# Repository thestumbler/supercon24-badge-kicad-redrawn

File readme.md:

# Redrawing Hackaday Supercon 2024 Badge in Kicad

Making a KiCad version of the Supercon 2024 Badge.
See the background story in this [Hackaday article](
https://hackaday.com/2024/10/31/supercon-2024-flower-sao-badge-redrawing-in-kicad).

* [Schematic drawing (PDF)](badge24-schematic.pdf))
* [PCB top drawing (PDF)](badge24-pcb-top.pdf)
* [PCB bottom drawing (PDF)](badge24-pcb-bot.pdf)

## Original Drawings

* [Schematic drawing (PDF)](badge24-original-sch.pdf)
* [PCB top drawing (PDF)](badge24-original-pcb-top.pdf)
* [PCB bottom drawing (PDF)](badge24-original-pcb-bot.pdf)

* [Assembly BOM (XLSX)](badge24-original-and-petal-matrix-bom.xlsx)

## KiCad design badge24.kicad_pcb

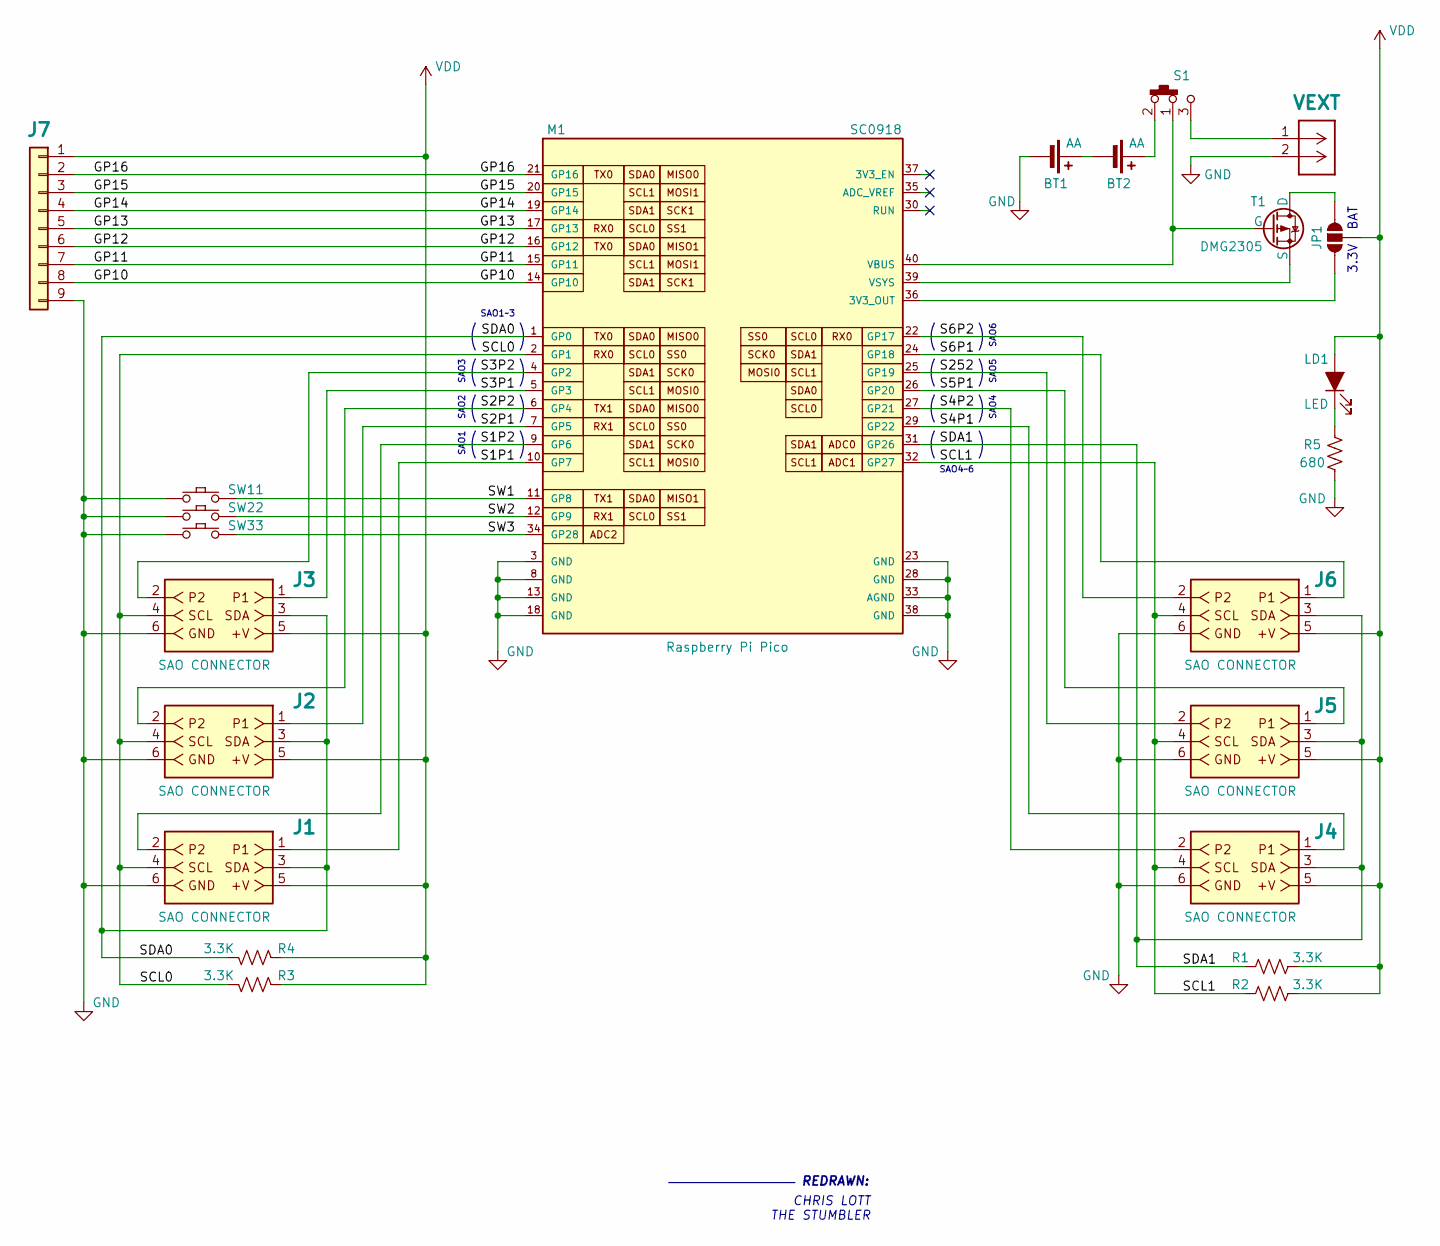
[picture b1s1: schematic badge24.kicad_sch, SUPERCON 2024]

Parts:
BT1, BT2: AA; BatteryHolder_Keystone_2460_1xAA_SAO
J1, J2, J3, J4, J5, J6: SAO CONNECTOR; SAO_PIN_HEADER_2x03
J7: Conn_01x09; IO_SAO_1x09_SMD_EXTERNAL
J99: VEXT; SAO_PinHeader_1x02_P2.54mm_SMD
JP1: SolderJumper_3_Open; SolderJumper_Open_Rounded_SAO
LD1: LED; LED_0805_2012Metric
M1: SC0918; RPi_Pico_SMD_SAO; PARTREV 1.6
R1, R2, R3, R4: 3.3K; R_0603_1608Metric_SAO
R5: 680; R_0603_1608Metric_SAO
S1: SW_Slide_SPDT; SW_Slide-03_Wuerth-WS-SLTV_10x2.5x6.4_P2.54mm
SW11, SW22, SW33: SW_Push; SW_SPST_PTS645_SAO
T1: DMG2305; SOT-23_SAO

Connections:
/GP10: J7.8, M1.14 (GP10)
/GP11: J7.7, M1.15 (GP11)
/GP12: J7.6, M1.16 (GP12)
/GP13: J7.5, M1.17 (GP13)
/GP14: J7.4, M1.19 (GP14)
/GP15: J7.3, M1.20 (GP15)
/GP16: J7.2, M1.21 (GP16)
/S1P1: J1.1, M1.10 (GP7)
/S1P2: J1.2, M1.9 (GP6)
/S2P1: J2.1, M1.7 (GP5)
/S2P2: J2.2, M1.6 (GP4)
/S3P1: J3.1, M1.5 (GP3)
/S3P2: J3.2, M1.4 (GP2)
/S4P1: J4.1, M1.29 (GP22)
/S4P2: J4.2, M1.27 (GP21)
/S5P1: J5.1, M1.26 (GP20)
/S6P1: J6.1, M1.24 (GP18)
/S6P2: J6.2, M1.22 (GP17)
/S252: J5.2, M1.25 (GP19)
/SCL0: J1.4, J2.4, J3.4, M1.2 (GP1), R3.2
/SCL1: J4.4, J5.4, J6.4, M1.32 (GP27), R2.1
/SDA0: J1.3, J2.3, J3.3, M1.1 (GP0), R4.2
/SDA1: J4.3, J5.3, J6.3, M1.31 (GP26), R1.1
/SW1: M1.11 (GP8), SW11.2
/SW2: M1.12 (GP9), SW22.2
/SW3: M1.34 (GP28), SW33.1
GND: BT1.2 (-), J1.6, J2.6, J3.6, J4.6, J5.6, J6.6, J7.9, J99.2, M1.3 (GND), M1.8 (GND), M1.13 (GND), M1.18 (GND), M1.23 (GND), M1.28 (GND), M1.33 (AGND), M1.38 (GND), R5.2, SW11.1, SW22.1, SW33.2
unnamed: BT1.1 (+), BT2.2 (-)
unnamed: BT2.1 (+), S1.2 (A)
unnamed: J99.1, S1.3 (B)
unnamed: JP1.1 (A), T1.3 (D)
unnamed: JP1.3 (B), M1.36 (3V3_OUT)
unnamed: LD1.1 (K), R5.1
unnamed: M1.40 (VBUS), S1.1 (C), T1.1 (G)
unnamed: M1.39 (VSYS), T1.2 (S)
VDD: J1.5, J2.5, J3.5, J4.5, J5.5, J6.5, J7.1, JP1.2 (C), LD1.2 (A), R1.2, R2.2, R3.1, R4.1

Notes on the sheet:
SAO4
REDRAWN:
SAO5
SAO1
BAT
SAO6
SAO3
SAO4~6
3.3V
CHRIS LOTT THE STUMBLER
SAO2
SAO1~3

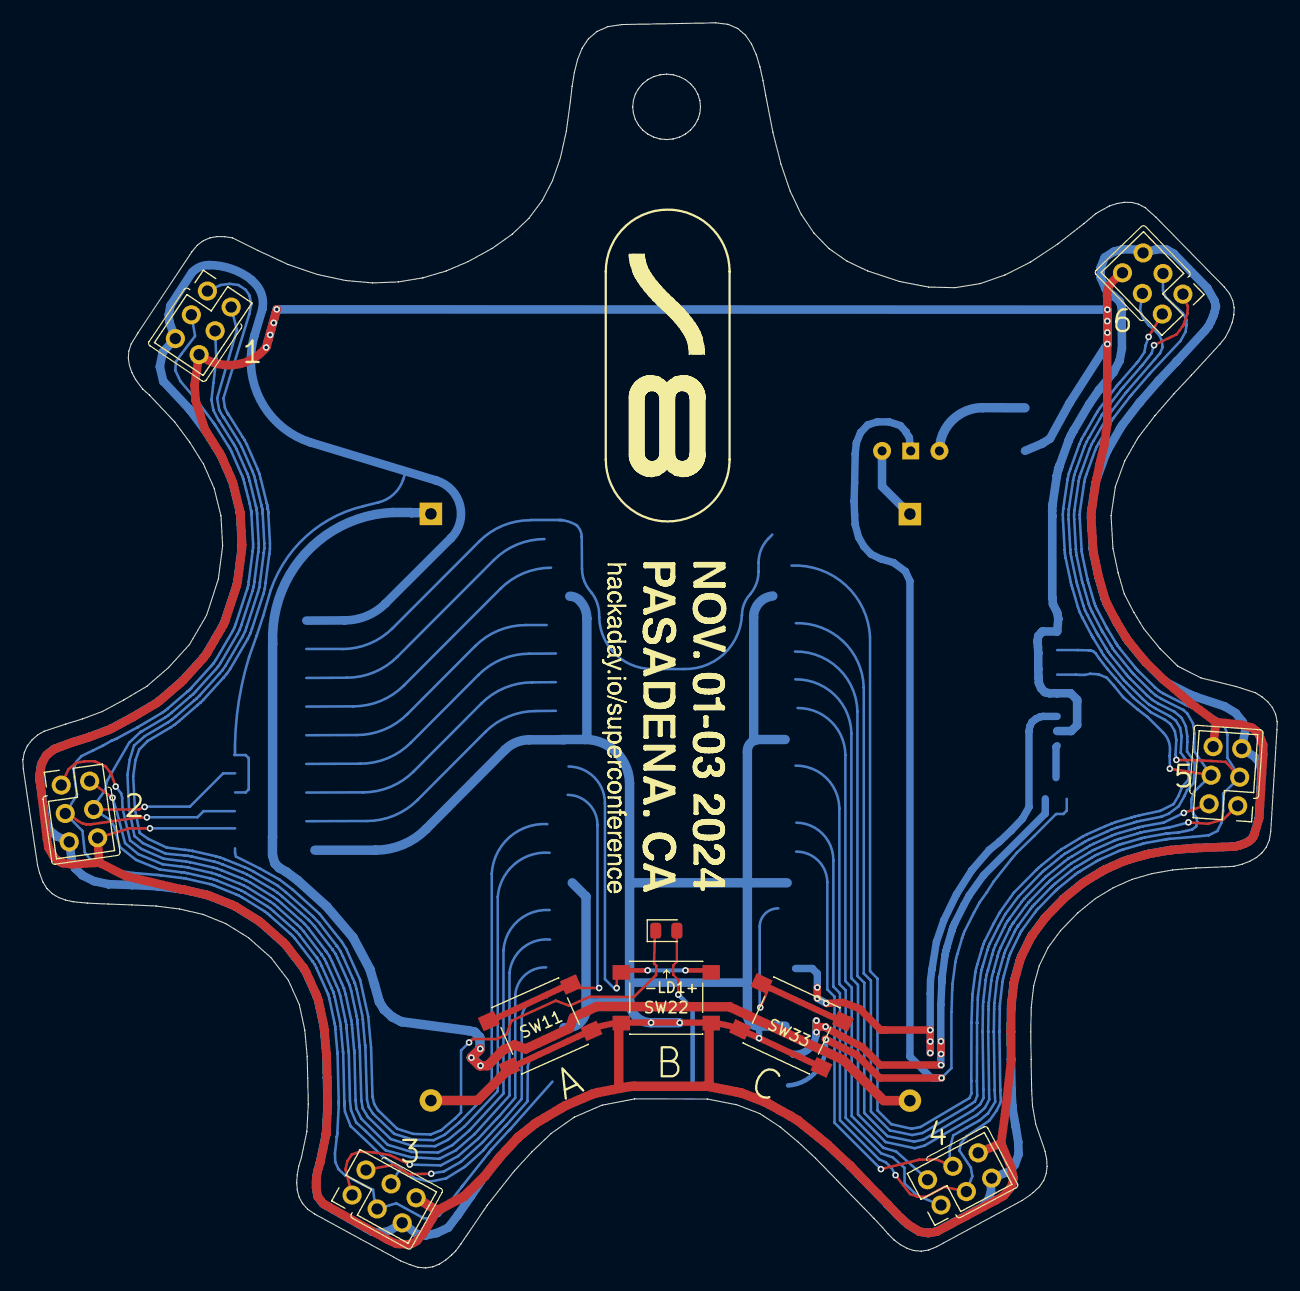
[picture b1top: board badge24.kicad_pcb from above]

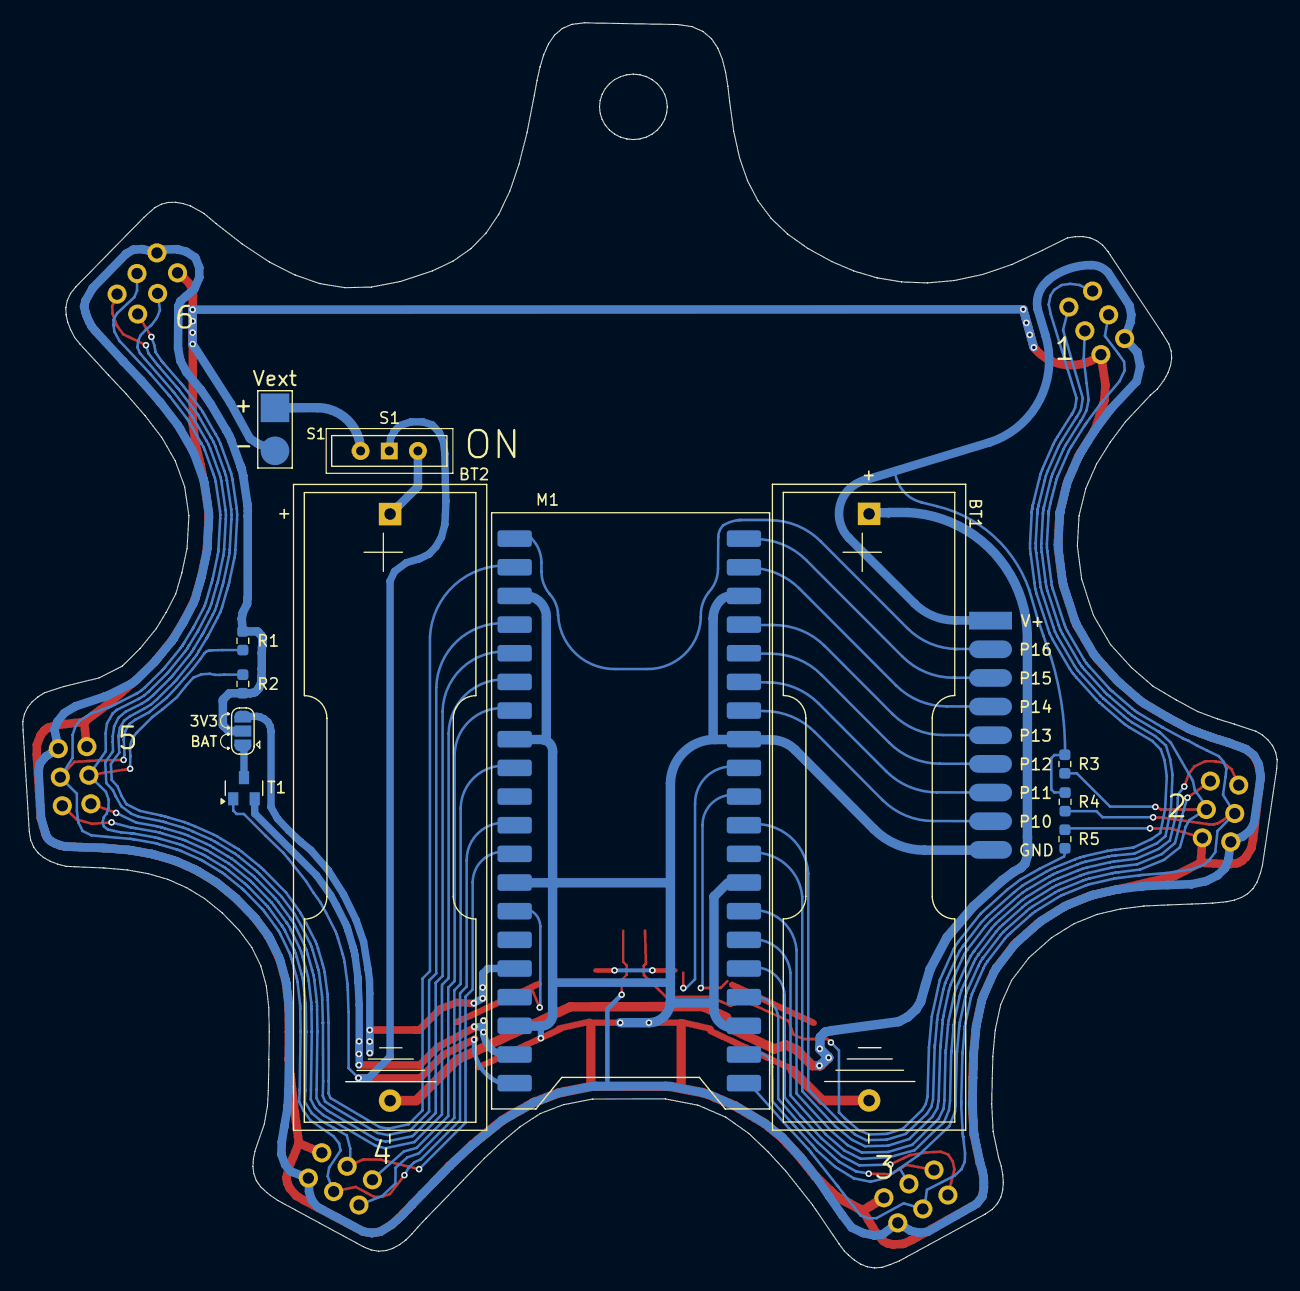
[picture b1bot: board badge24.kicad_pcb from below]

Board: 2 copper layers, 111.2 x 110.3 mm, 23 parts (13 on the bottom side), 36 nets.

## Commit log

2024-10-27 initial release
2024-10-27 edited readme
2024-10-30 clean up for writeup
2024-10-30 merged images
2024-10-30 added images of pdf
2024-10-31 added original schematic sheet
2024-10-31 corrected image filename
2024-10-31 added jolly wrencher
2024-11-01 added Hackaday article links
